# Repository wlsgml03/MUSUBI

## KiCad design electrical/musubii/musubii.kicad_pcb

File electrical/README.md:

this is the old electrical stuff! this stuff is bad! dont look at this stuff ever again!

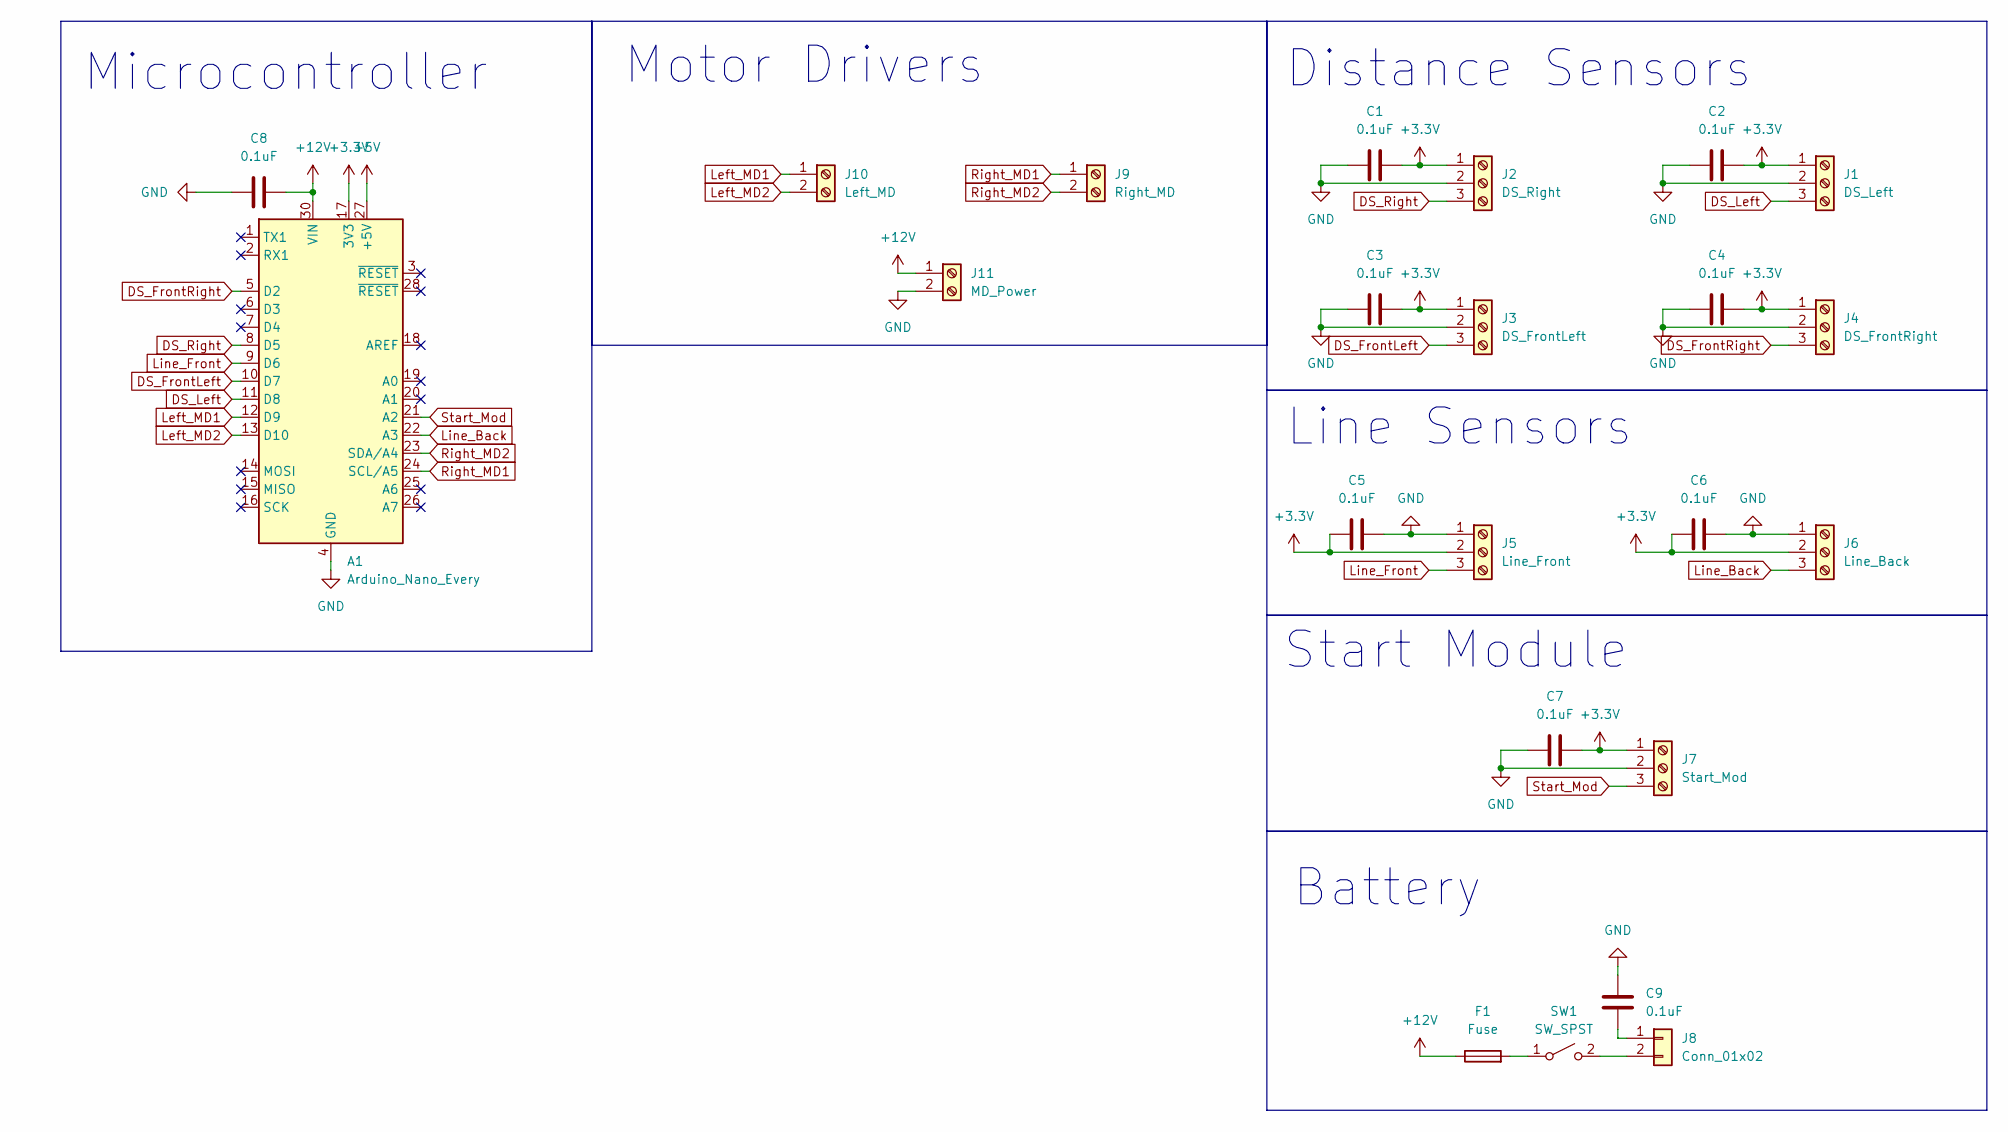
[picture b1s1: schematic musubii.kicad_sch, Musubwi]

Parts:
A1: Arduino_Nano_Every; Arduino_Nano
C1, C2, C3, C4, C5, C6, C7, C8, C9: 0.1uF; C_0805_2012Metric_Pad1.18x1.45mm_HandSolder
F1: Fuse; FUSC3215X83N
J1: DS_Left; JST_PH_S3B-PH-K_1x03_P2.00mm_Horizontal
J2: DS_Right; JST_PH_S3B-PH-K_1x03_P2.00mm_Horizontal
J3: DS_FrontLeft; JST_PH_S3B-PH-K_1x03_P2.00mm_Horizontal
J4: DS_FrontRight; JST_PH_S3B-PH-K_1x03_P2.00mm_Horizontal
J5: Line_Front; JST_PH_S3B-PH-K_1x03_P2.00mm_Horizontal
J6: Line_Back; JST_PH_S3B-PH-K_1x03_P2.00mm_Horizontal
J7: Start_Mod; JST_PH_S3B-PH-K_1x03_P2.00mm_Horizontal
J8: Conn_01x02; AMASS_XT60-F_1x02_P7.20mm_Vertical
J9: Right_MD; PhoenixContact_MSTBA_2,5_2-G_1x02_P5.00mm_Horizontal
J10: Left_MD; PhoenixContact_MSTBA_2,5_2-G_1x02_P5.00mm_Horizontal
J11: MD_Power; PhoenixContact_MSTBA_2,5_2-G_1x02_P5.00mm_Horizontal
SW1: SW_SPST; SW_JS102011JCQN

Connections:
+3.3V: A1.17 (3V3), C1.1, C2.1, C3.1, C4.1, C5.2, C6.2, C7.1, J1.1, J2.1, J3.1, J4.1, J5.2, J6.2, J7.1
+5V: A1.27 (+5V)
+12V: A1.30 (VIN), C8.2, F1.1, J11.1
DS_FrontLeft: A1.10 (D7), J3.3
DS_FrontRight: A1.5 (D2), J4.3
DS_Left: A1.11 (D8), J1.3
DS_Right: A1.8 (D5), J2.3
GND: A1.4 (GND), A1.29 (GND), C1.2, C2.2, C3.2, C4.2, C5.1, C6.1, C7.2, C8.1, C9.2, J1.2, J2.2, J3.2, J4.2, J5.1, J6.1, J7.2, J11.2
Left_MD1: A1.12 (D9), J10.1
Left_MD2: A1.13 (D10), J10.2
Line_Back: A1.22 (A3), J6.3
Line_Front: A1.9 (D6), J5.3
unnamed: C9.1, J8.1
unnamed: J8.2, SW1.2 (B)
unnamed: F1.2, SW1.1 (A)
Right_MD1: A1.24 (SCL/A5), J9.1
Right_MD2: A1.23 (SDA/A4), J9.2
Start_Mod: A1.21 (A2), J7.3

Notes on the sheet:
Battery
Motor Drivers
Distance Sensors
Line Sensors
Microcontroller
Start Module

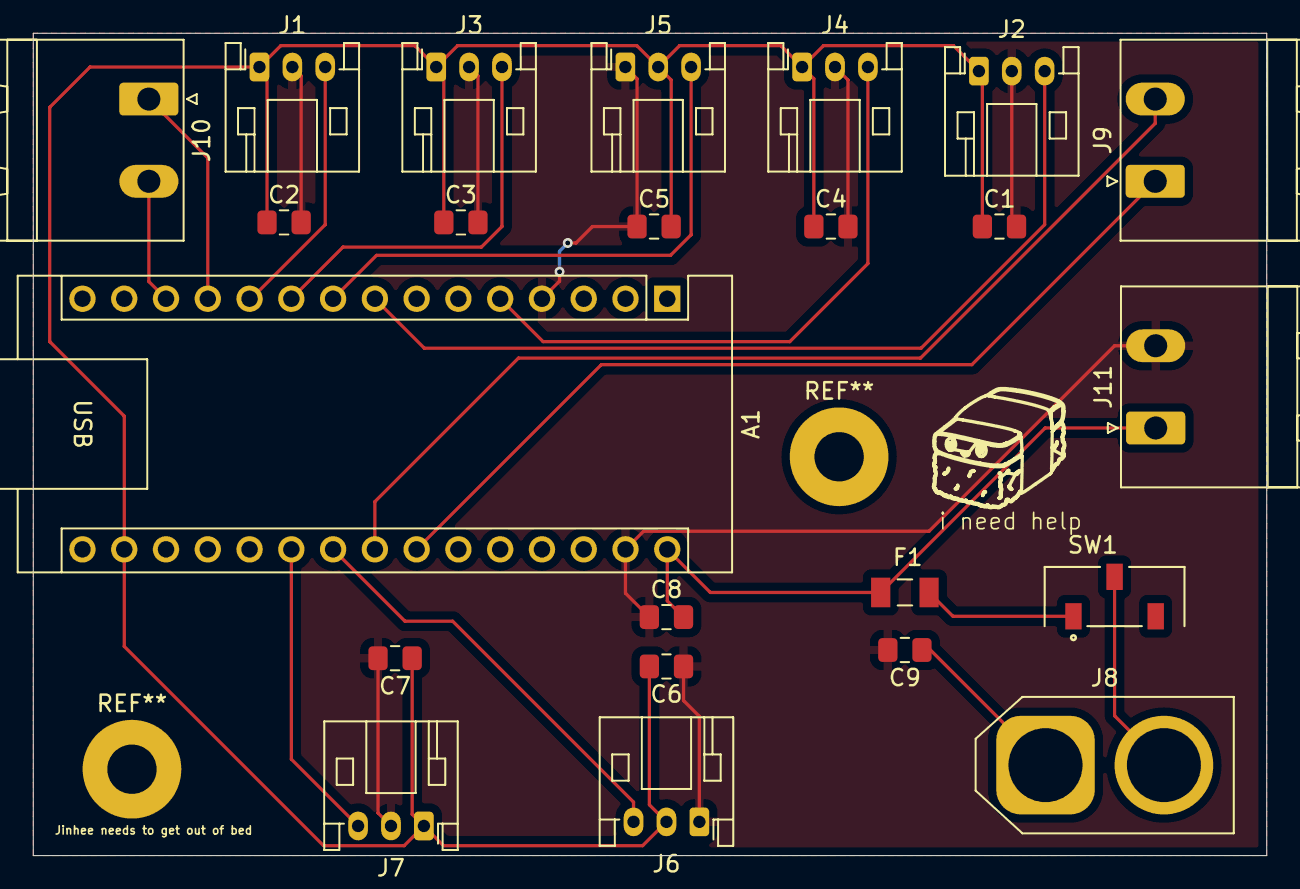
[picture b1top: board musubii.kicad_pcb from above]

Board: 2 copper layers, 75.0 x 50.0 mm, 23 parts (0 on the bottom side), 17 nets.

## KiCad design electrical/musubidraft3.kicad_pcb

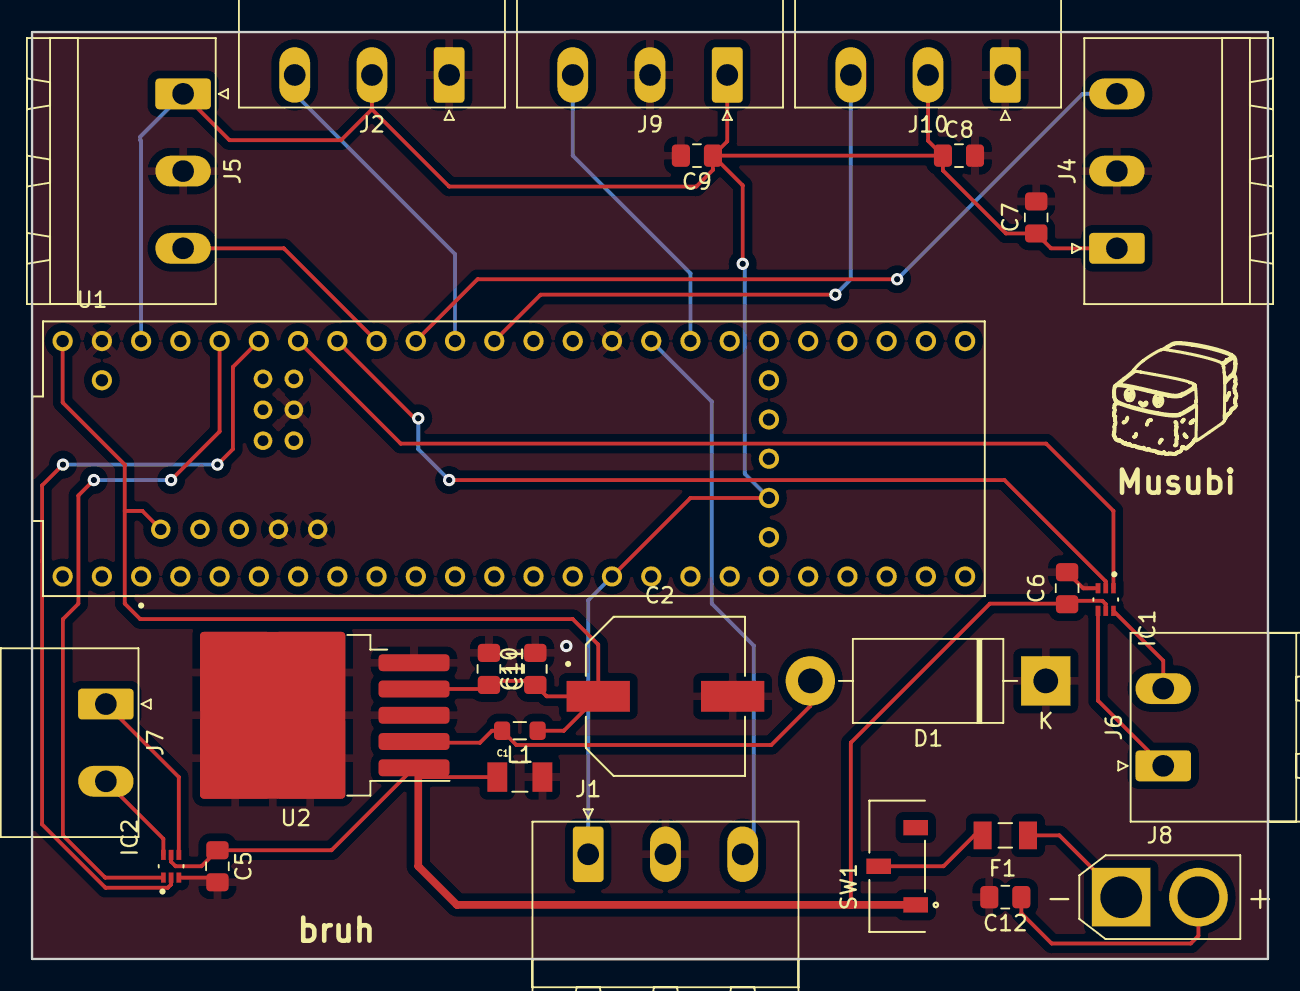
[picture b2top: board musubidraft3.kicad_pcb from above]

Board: 2 copper layers, 80.0 x 60.0 mm, 27 parts (0 on the bottom side), 22 nets.

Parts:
C1: 100uF; CAPC3216X190N
C2: 220uF; CAP_EEHZS1H221P
C5, C6, C7, C8, C9, C10, C11, C12: 0.1uF; C_0805_2012Metric_Pad1.18x1.45mm_HandSolder
D1: 1N5822; D_DO-201AD_P15.24mm_Horizontal
F1: Fuse; FUSC3215X83N
IC1, IC2: DRV8212DRLR; SOT50P160X60-6N
J1: DDS3; PhoenixContact_MSTBA_2,5_3-G_1x03_P5.00mm_Horizontal
J2, J10: Screw_Terminal_01x03; PhoenixContact_MSTBA_2,5_3-G_1x03_P5.00mm_Horizontal
J4: DDS1; PhoenixContact_MSTBA_2,5_3-G_1x03_P5.00mm_Horizontal
J5: DDS2; PhoenixContact_MSTBA_2,5_3-G_1x03_P5.00mm_Horizontal
J6: BDC1; PhoenixContact_MSTBA_2,5_2-G_1x02_P5.00mm_Horizontal
J7: BDC2; PhoenixContact_MSTBA_2,5_2-G_1x02_P5.00mm_Horizontal
J8: Battery; AMASS_XT30U-M_1x02_P5.0mm_Vertical
J9: DDS4; PhoenixContact_MSTBA_2,5_3-G_1x03_P5.00mm_Horizontal
L1: 100uH; L_0805_2012Metric_Pad1.05x1.20mm_HandSolder
SW1: SW_SPST; SW_JS102011JCQN
U1: DEV-16771; MODULE_DEV-16771
U2: LM2576S-5; TO-263-5_TabPin3

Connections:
+3.3V: C7.1, C8.1, C9.1, J1.1, J2.2, J4.1, J5.1, J9.1, J10.2, U1.3.3V_1 (3.3V), U1.3.3V_2 (3.3V), U1.3.3V_3 (3.3V)
+5V: C2.1, C10.1, C11.2, L1.1, U1.5V, U1.VIN, U2.4 (FB)
+12V: C1.1, C5.1, C6.1, IC1.5 (VM), IC2.5 (VM), SW1.1 (A), U2.1 (VIN)
DDS_1: J4.3, U1.17 (A3)
DDS_2: J5.3, U1.18 (A4)
DDS_3: J1.3, U1.41 (A17)
DDS_4: J9.3, U1.40 (A16)
GND: C1.2, C2.2, C5.2, C6.2, C7.2, C8.2, C9.2, C10.2, C11.1, C12.2, D1.1 (K), IC1.3 (GND), IC2.3 (GND), J1.2, J2.1, J4.2, J5.2, J9.2, J10.1, U1.GND1 (GND), U1.GND2 (GND), U1.GND3 (GND), U1.GND4 (GND), U1.GND5 (GND), U1.USB_GND1 (USB_GND), U1.USB_GND2 (USB_GND), U2.3 (GND), U2.5 (~ON/OFF)
L_LINE: J2.3, U1.16 (A2)
MD1: IC1.2 (IN2), U1.19 (A5)
MD2: IC1.1 (IN1), U1.20 (A6)
MD3: IC2.2 (IN2), U1.21 (A7)
MD4: IC2.1 (IN1), U1.22 (A8)
unnamed: D1.2 (A), L1.2, U2.2 (OUT)
unnamed: IC1.6 (OUT1), J6.2
unnamed: IC1.4 (OUT2), J6.1
unnamed: IC2.6 (OUT1), J7.2
unnamed: IC2.4 (OUT2), J7.1
unnamed: F1.1, J8.1
unnamed: C12.1, J8.2
unnamed: F1.2, SW1.2 (B)
R_LINE: J10.3, U1.15 (A1)

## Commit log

2024-08-07 Add files via upload
    testing- first iteration of musubi code file
2024-08-07 Create musubii
2024-08-07 Electrical folder for musubii
2024-08-07 Create tldr
2024-08-07 picture upload
    dont worry about it u didnt see this
2024-08-07 exec
    execution :3
2024-08-07 Create bruh.txt
    bruh
2024-08-07 brainrot spectrum
    old spectrum, needs to be updated bc i am not a degenerate
2024-08-07 musubi logo (png)
    has transparent bg
2024-08-07 musubi logo (dxf)
    it is the correct size and ready for importing to kicad
2024-08-07 musubii kicad
    that is a lot of junk i hope it doesn't blow anything up! :3
2024-08-07 Delete electrical/musubii
    idk why this is here
2024-08-07 questionable screenshot
    definitely legal
2024-08-08 jinhee drinks water
    proof that jinhee drinks more water than me
2024-08-08 definitely blackmail
    blob
2024-08-08 Create README.md
    basically says the stuff here is old
2024-08-08 added old musubi electrical
    this stuff sucks dont open it (like not even funny at all)
2024-08-29 jinhee is torturing me help
2024-09-01 added some direction functions
2024-09-01 pcb layout image holy s im tired
2024-09-06 yare yare (software pin assignment update)
2024-09-14 updated xanders nasty
2024-09-14 line sensor testing
2024-10-04 transferring musubii to laptop
